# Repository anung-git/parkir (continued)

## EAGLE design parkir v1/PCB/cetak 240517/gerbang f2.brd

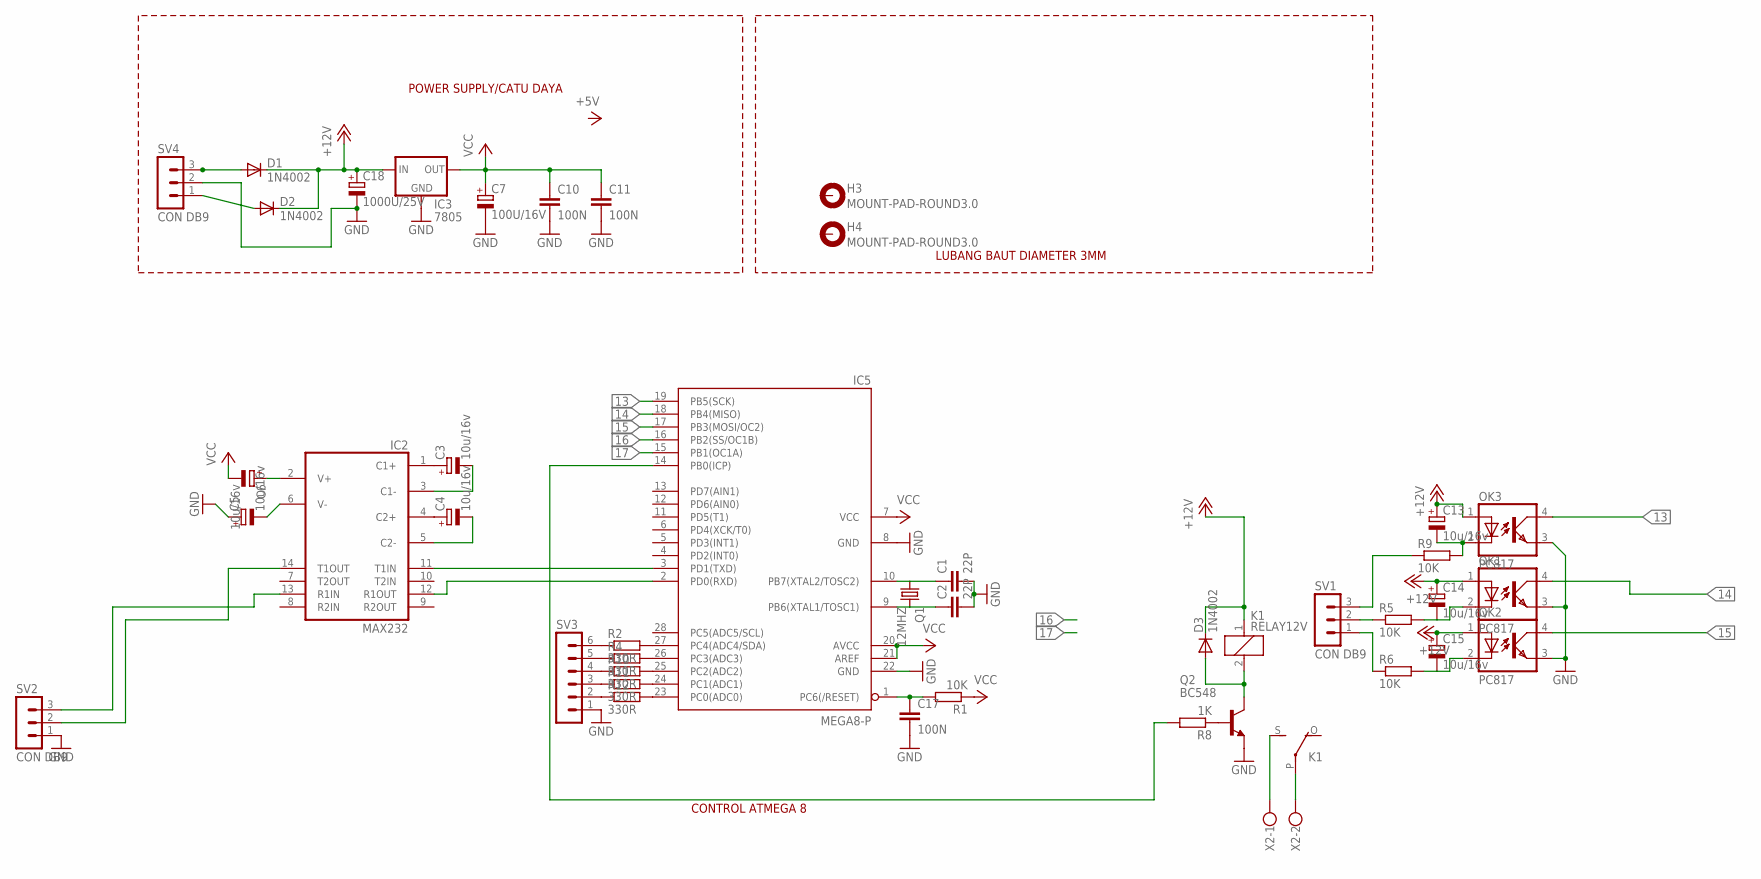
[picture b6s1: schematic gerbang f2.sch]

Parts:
C1, C2: 22P; C025-025X050
C3, C4, C5, C6, C13, C14, C15: 10u/16v; E2,5-6
C7: 100U/16V; E2,5-6
C10, C11, C17: 100N; C025-025X050
C18: 1000U/25V; E5-8,5
D1, D2, D3: 1N4002; DO35-10
H3, H4: MOUNT-PAD-ROUND3.0; 3,0-PAD
IC2: MAX232; DIL16
IC3: 7805; 78XXS
IC5: MEGA8-P; DIL28-3
K1: RELAY12V; ZF112
OK1, OK2, OK3: PC817; DIL04
Q1: 12MHZ; HC49U-V
Q2: BC548; TO92-EBC
R1: 10K; 0207/10
R2, R4, R10, R11, R12: 330R; 0204V
R5, R6, R9: 10K; 0204V
R8: 1K; 0207/10
SV1, SV2, SV4: CON DB9; MA03-1
SV3: MA06-1
X2: W237-102

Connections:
13: IC5.19 (PB5(SCK)), OK3.4 (COL)
14: IC5.18 (PB4(MISO)), OK1.4 (COL)
15: IC5.17 (PB3(MOSI/OC2)), OK2.4 (COL)
16: IC5.16 (PB2(SS/OC1B))
17: IC5.15 (PB1(OC1A))
+12V: C13.+, C14.+, C15.+, C18.+, D1.C, D2.C, D3.C, IC3.IN, K1.1, OK1.1 (A), OK2.1 (A), OK3.1 (A)
GND: C1.2, C2.2, C5.+, C7.-, C10.2, C11.2, C17.2, C18.-, IC2.15 (GND), IC3.GND, IC5.8 (GND), IC5.22 (GND), OK1.3 (EMIT), OK2.3 (EMIT), OK3.3 (EMIT), Q2.E, SV2.1, SV3.1, SV4.2
unnamed: C17.1, IC5.1 (PC6(/RESET)), R1.2
unnamed: C6.+, IC2.2 (V+)
unnamed: C5.-, IC2.6 (V-)
unnamed: IC5.14 (PB0(ICP)), R8.2
unnamed: R5.1, SV1.2
unnamed: R6.1, SV1.1
unnamed: R9.1, SV1.3
unnamed: D1.A, SV4.3
unnamed: IC2.12 (R1OUT), IC5.2 (PD0(RXD))
unnamed: IC2.11 (T1IN), IC5.3 (PD1(TXD))
unnamed: C2.1, IC5.9 (PB6(XTAL1/TOSC1)), Q1.2
unnamed: C1.1, IC5.10 (PB7(XTAL2/TOSC2)), Q1.1
unnamed: C3.+, IC2.1 (C1+)
unnamed: C3.-, IC2.3 (C1-)
unnamed: D2.A, SV4.1
unnamed: IC5.27 (PC4(ADC4/SDA)), R2.2
unnamed: C4.+, IC2.4 (C2+)
unnamed: C4.-, IC2.5 (C2-)
unnamed: IC2.13 (R1IN), SV2.3
unnamed: IC2.14 (T1OUT), SV2.2
unnamed: K1.S, X2.1
unnamed: K1.P, X2.2
unnamed: C13.-, OK3.2 (C), R9.2
unnamed: C14.-, OK1.2 (C), R5.2
unnamed: C15.-, OK2.2 (C), R6.2
unnamed: D3.A, K1.2, Q2.C
unnamed: IC5.26 (PC3(ADC3)), R4.2
unnamed: Q2.B, R8.1
unnamed: IC5.25 (PC2(ADC2)), R10.2
unnamed: IC5.24 (PC1(ADC1)), R11.2
unnamed: IC5.23 (PC0(ADC0)), R12.2
unnamed: R2.1, SV3.6
unnamed: R4.1, SV3.5
unnamed: R10.1, SV3.4
unnamed: R11.1, SV3.3
unnamed: R12.1, SV3.2
VCC: C6.-, C7.+, C10.1, C11.1, IC2.16 (VCC), IC3.OUT, IC5.7 (VCC), IC5.20 (AVCC), IC5.21 (AREF), R1.1

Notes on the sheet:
POWER SUPPLY/CATU DAYA
CONTROL ATMEGA 8
LUBANG BAUT DIAMETER 3MM

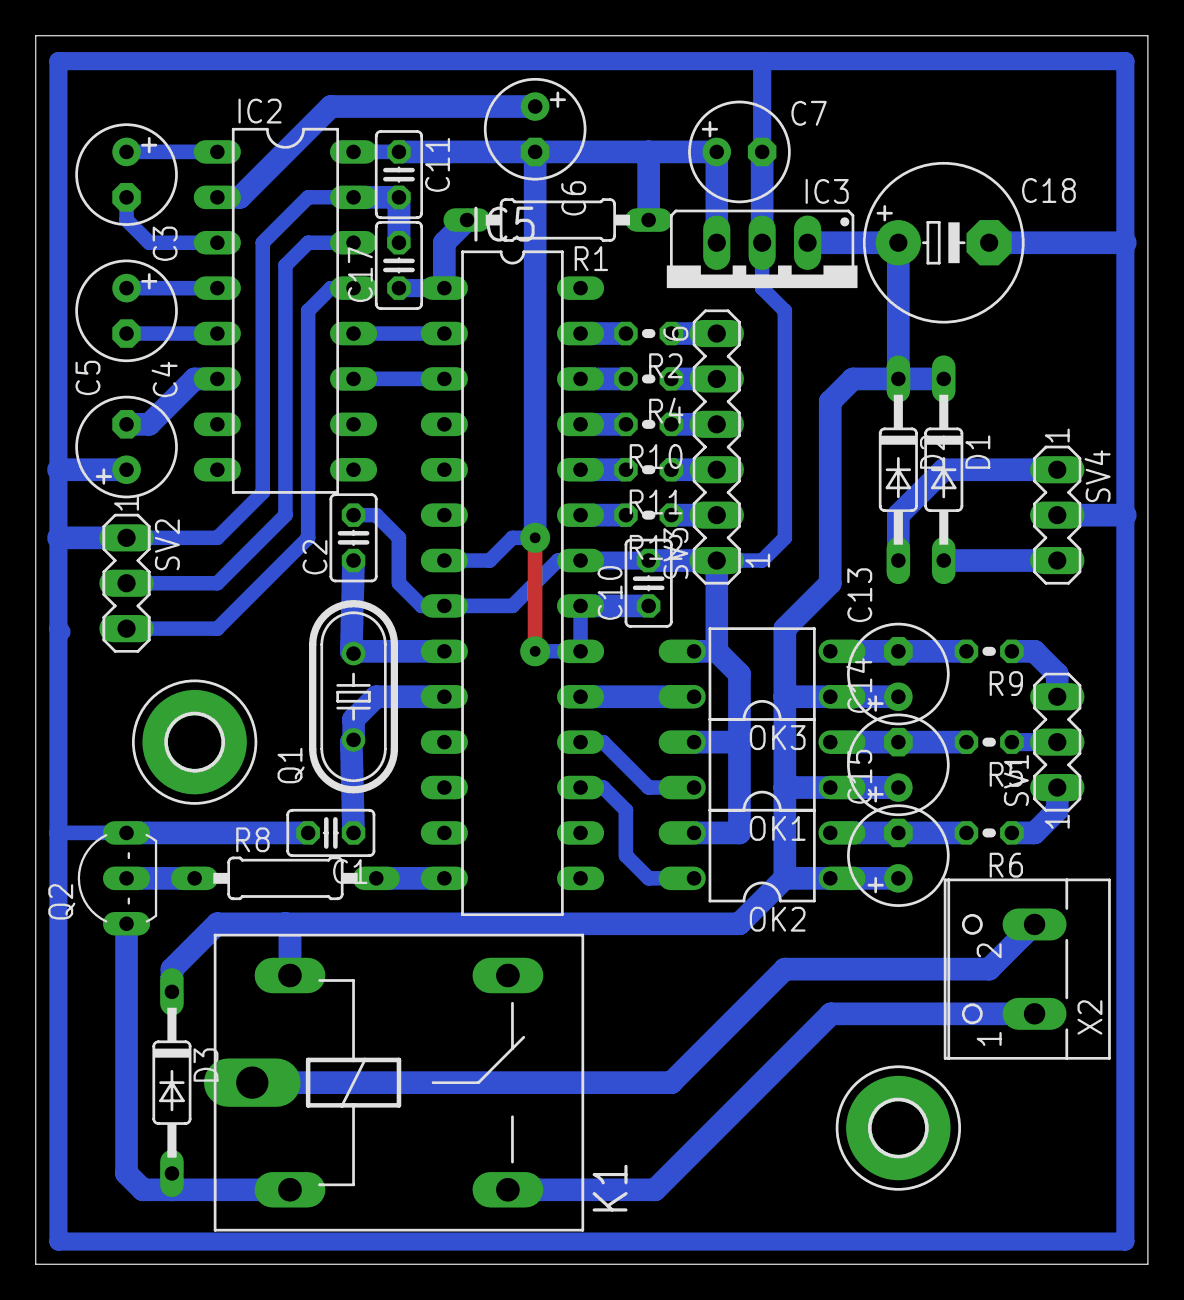
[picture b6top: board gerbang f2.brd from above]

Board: 2 copper layers, 62.2 x 68.7 mm, 43 parts (0 on the bottom side), 42 nets.

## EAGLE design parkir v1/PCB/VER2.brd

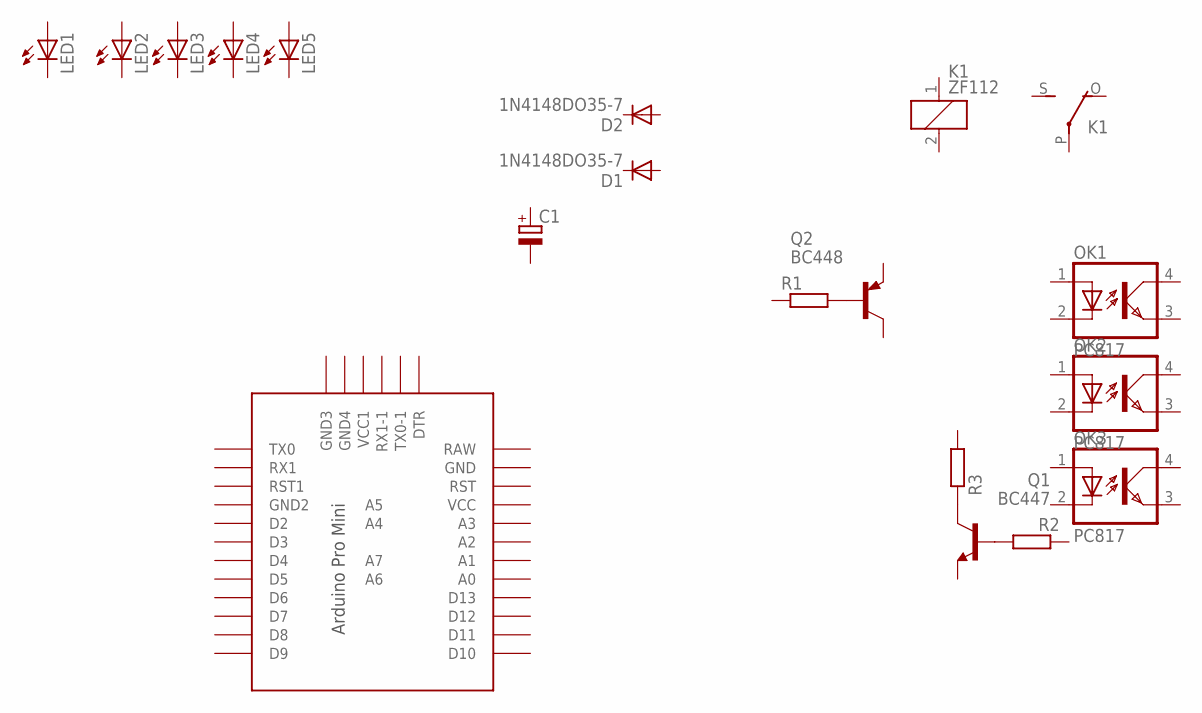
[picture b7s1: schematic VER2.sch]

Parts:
C1: CPOL-EUE5-6; E5-6
D1, D2: 1N4148DO35-7; DO35-7
K1: ZF112
LED1, LED2, LED3, LED4, LED5: LED5MM
OK1, OK2, OK3: PC817; DIL04
Q1: BC447; TO92-EBC
Q2: BC448; TO92-EBC
R1, R2, R3: R-EU_0207/7; 0207/7
U$1: PRO-MINI-2

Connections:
unnamed: Q2.B, R1.2
unnamed: Q1.B, R2.2
unnamed: Q1.C, R3.1

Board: 2 copper layers, 18 parts (0 on the bottom side), 3 nets, no tracks yet.

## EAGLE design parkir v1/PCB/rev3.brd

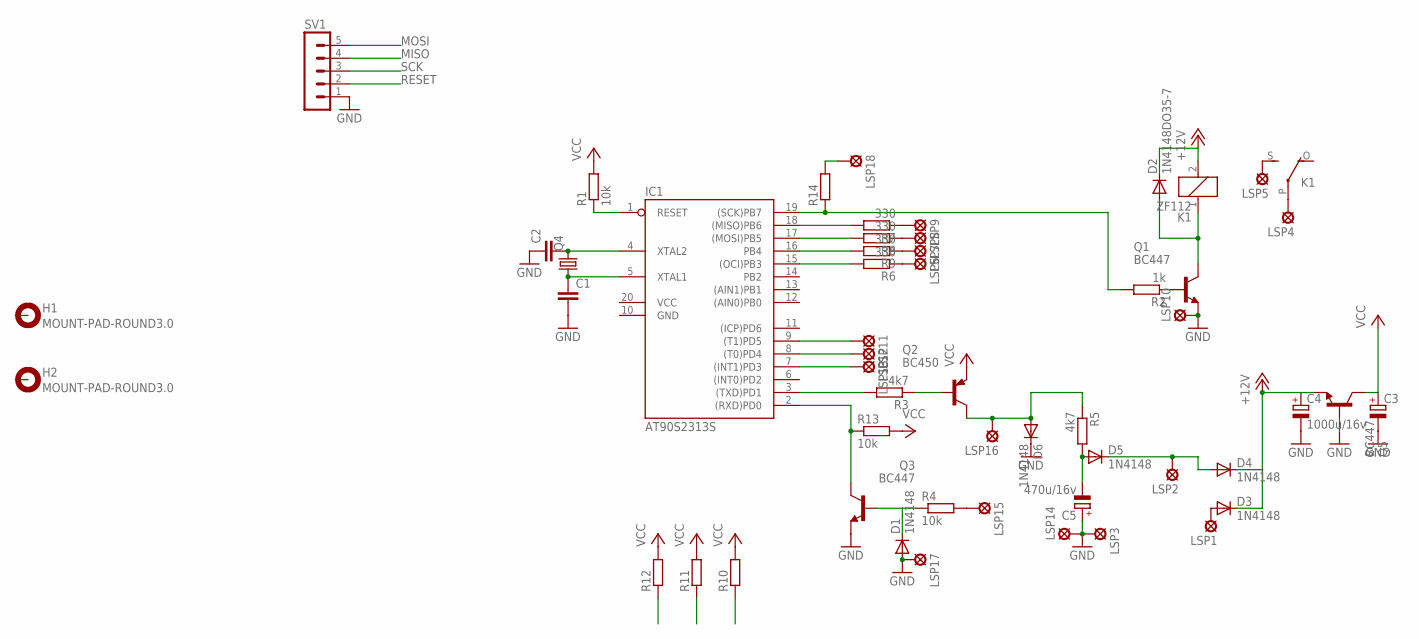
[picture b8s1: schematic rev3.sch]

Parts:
C1, C2: C-EU025-025X050; C025-025X050
C3: CPOL-EUE2.5-5; E2,5-5
C4: 1000u/16v; E5-6
C5: 470u/16v; E5-6
D1, D3, D4, D5, D6: 1N4148; DO35-7
D2: 1N4148DO35-7; DO35-7
H1, H2: MOUNT-PAD-ROUND3.0; 3,0-PAD
IC1: AT90S2313S; SO20L
K1: ZF112
LSP1, LSP2, LSP3, LSP4, LSP5, LSP6, LSP7, LSP8, LSP9, LSP10, LSP11, LSP12, LSP13, LSP14, LSP15, LSP16, LSP17, LSP18: MCS10B
Q1, Q3, Q5: BC447; TO92-EBC
Q2: BC450; TO92-EBC
Q4: CRYSTALHC49S; HC49/S
R1, R4, R13: 10k; 0207/7
R2: 1k; 0207/7
R3, R5: 4k7; 0207/7
R6, R7, R8, R9: 330; 0207/7
R10, R11, R12: R-EU_0207/7; 0207/7
R14: R-EU_0207/10; 0207/10
SV1: MA05-1

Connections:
+12V: C4.+, D2.C, D3.C, D4.C, K1.2, Q5.E
A: IC1.9 ((T1)PD5), LSP11.MP, R10.1
B: IC1.8 ((T0)PD4), LSP12.MP, R11.1
C: IC1.7 ((INT1)PD3), LSP13.MP, R12.1
GND: C1.2, C2.1, C3.-, C4.-, C5.+, D1.A, D6.C, IC1.10 (GND), LSP3.MP, LSP10.MP, LSP14.MP, LSP17.MP, Q1.E, Q3.E, Q5.B, SV1.1
MISO: IC1.18 ((MISO)PB6), R7.2, SV1.4
MOSI: IC1.17 ((MOSI)PB5), R8.2, SV1.5
unnamed: D6.A, LSP16.MP, Q2.C, R5.1
unnamed: C2.2, IC1.4 (XTAL2), Q4.2
unnamed: C1.1, IC1.5 (XTAL1), Q4.1
unnamed: D3.A, LSP1.MP
unnamed: Q1.B, R2.1
unnamed: Q2.B, R3.1
unnamed: D1.C, Q3.B, R4.1
unnamed: D2.A, K1.1, Q1.C
unnamed: IC1.15 ((OCI)PB3), R6.2
unnamed: C5.-, D5.A, R5.2
unnamed: IC1.3 ((TXD)PD1), R3.2
unnamed: IC1.2 ((RXD)PD0), Q3.C, R13.1
unnamed: K1.P, LSP4.MP
unnamed: K1.S, LSP5.MP
unnamed: D4.A, D5.C, LSP2.MP
unnamed: IC1.16 (PB4), R9.2
unnamed: LSP6.MP, R6.1
unnamed: LSP7.MP, R9.1
unnamed: LSP8.MP, R8.1
unnamed: LSP9.MP, R7.1
unnamed: LSP15.MP, R4.2
unnamed: LSP18.MP, R14.2
RESET: IC1.1 (RESET), R1.1, SV1.2
SCK: IC1.19 ((SCK)PB7), R2.2, R14.1, SV1.3
VCC: C3.+, IC1.20 (VCC), Q2.E, Q5.C, R1.2, R10.2, R11.2, R12.2, R13.2

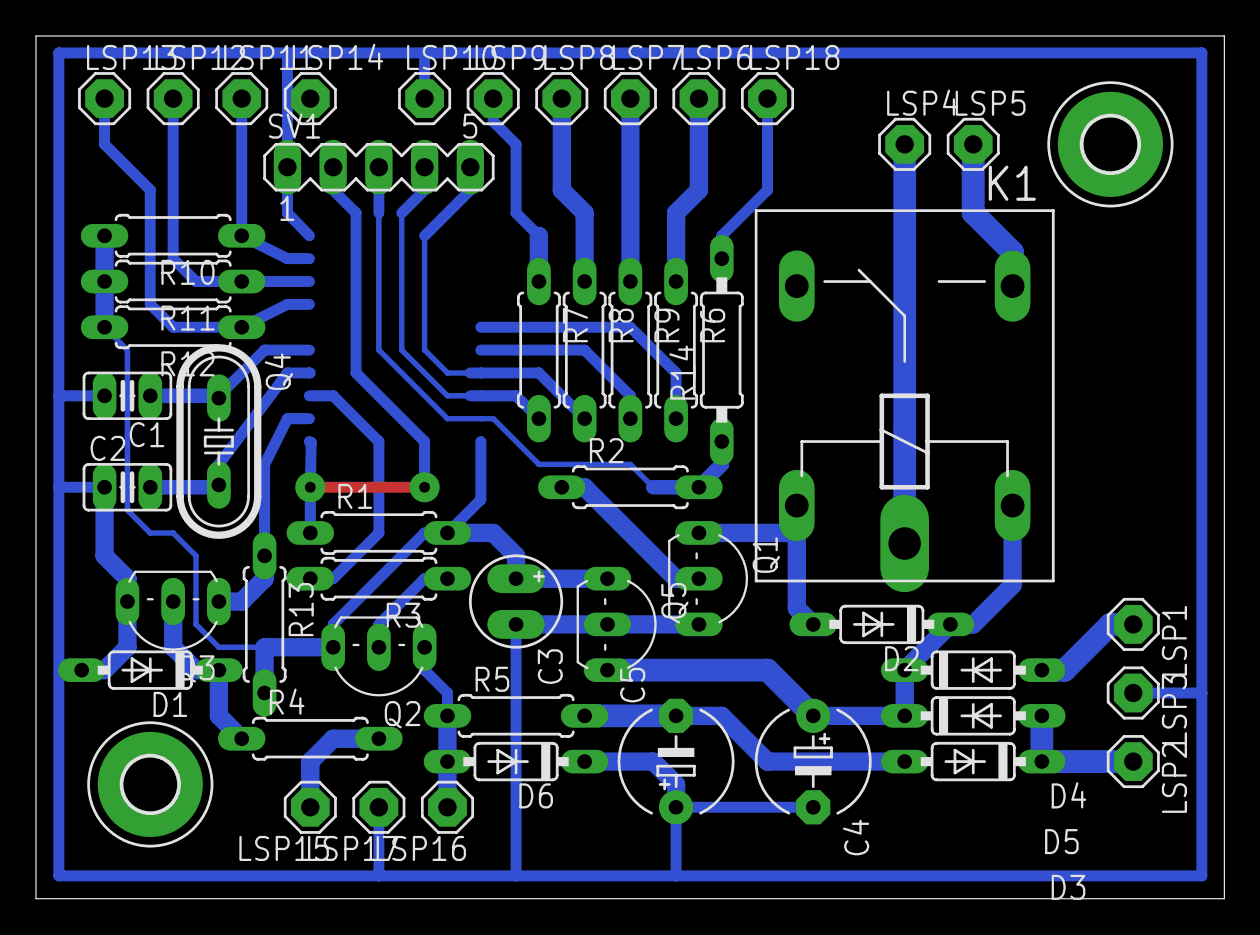
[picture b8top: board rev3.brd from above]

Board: 2 copper layers, 66.0 x 47.9 mm, 53 parts (1 on the bottom side), 32 nets.

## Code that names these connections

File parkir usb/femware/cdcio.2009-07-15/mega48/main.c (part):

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
#define port_relay PORTB
#define ddr_relay DDRB
#define pin_relay PB2

#define pin_input PINB
#define ddr_input DDRB
#define input_1 PB5
#define input_2 PB4
#define input_3 PB3

volatile unsigned int time=0;
enum {
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
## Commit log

2019-08-30 Add new file
2019-09-15 tambah versi sebelumnya
2019-09-15 upload versi usb
2020-12-26 update pcb
2020-12-27 program
2021-01-01 tambah watchdog
2021-01-01 relayout
2021-01-01 int16 to int8
